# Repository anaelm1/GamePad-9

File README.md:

# GamePad 9

GamePad 9 is a 9 key macropad with a rotary encoder, an OLED Display. It uses KMK firmware

It is made as a dedicated macropad for gaming (first person or racing games etc).

## Features:
- 3D printed body with a honeycomb design to show the PCB. 
- 128x32 OLED Display.
- EC11 Rotary encoder to increase/decrease the volume, and skip to the next song.
- 9 Keys (Tab, W, E, A, S, D, Shift, Space, Control).

## CAD Model:
The pcb is attached to the base at a height of 2mm using 4 M3 screws for optimal support. The top plate is attached to the body using M3 screws and heat inserts in the 4 corners. 

It has 2 separate printed pieces. The base where the PCB sits, and the top cover. The project name and my name is engraved on the top plate as well.

Made in Fusion360. 

## PCB
Here's my PCB! It was made in KiCad.

Schematic

PCB

## Firmware Overview
This hackpad uses KMK firmware for everything. 

- the rotary encoder changes volume. press to next song.
- The 9 keys are Tab, W, E, A, S, D, Shift, Space, Control.
- The OLED is text. (Will change to an animation in the future)

## BOM:
These are the components used in the GamePad 9:

- 9x Cherry MX Switches.
- 9x DSA Keycaps.
- 4x M3x5x4 Heatset inserts.
- 8x M3x16mm Screws. (These might be changed if other screw sizes suit better)
- 9x 1N4148 DO-35 Diodes.
- 1x 0.91" 128x32 OLED Display
- 1x EC11 Rotary Encoder
- 1x XIAO RP2040
- 1x Case (2 printed parts)

## Info:
This macropad is made as part of the Hack Club Hackpad program!

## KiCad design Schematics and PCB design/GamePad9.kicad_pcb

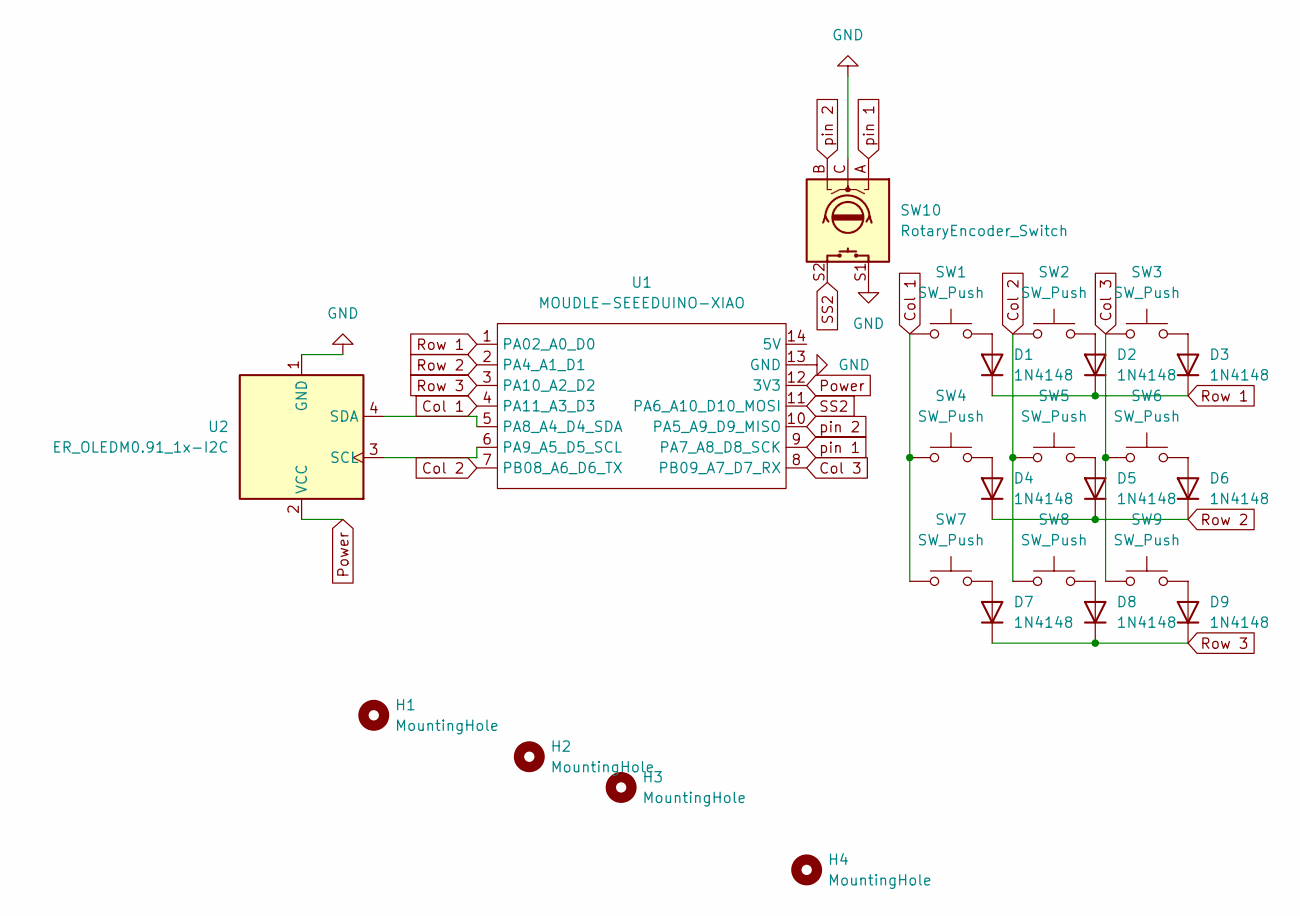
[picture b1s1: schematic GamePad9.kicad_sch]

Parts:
D1, D2, D3, D4, D5, D6, D7, D8, D9: 1N4148; D_DO-35_SOD27_P7.62mm_Horizontal
H1, H2, H3, H4: MountingHole; MountingHole_3.2mm_M3
SW1, SW2, SW3, SW4, SW5, SW6, SW7, SW8, SW9: SW_Push; SW_Cherry_MX_1.00u_PCB
SW10: RotaryEncoder_Switch; RotaryEncoder_Alps_EC11E-Switch_Vertical_H20mm
U1: MOUDLE-SEEEDUINO-XIAO; XIAO-Generic-Hybrid-14P-2.54-21X17.8MM
U2: ER_OLEDM0.91_1x-I2C

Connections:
Col 1: SW1.1, SW4.1, SW7.1, U1.4 (PA11_A3_D3)
Col 2: SW2.1, SW5.1, SW8.1, U1.7 (PB08_A6_D6_TX)
Col 3: SW3.1, SW6.1, SW9.1, U1.8 (PB09_A7_D7_RX)
GND: SW10.C, SW10.S1, U1.13 (GND), U2.1 (GND)
unnamed: D1.2 (A), SW1.2
unnamed: D2.2 (A), SW2.2
unnamed: D3.2 (A), SW3.2
unnamed: D4.2 (A), SW4.2
unnamed: D5.2 (A), SW5.2
unnamed: D6.2 (A), SW6.2
unnamed: D7.2 (A), SW7.2
unnamed: D8.2 (A), SW8.2
unnamed: D9.2 (A), SW9.2
unnamed: U1.5 (PA8_A4_D4_SDA), U2.4 (SDA)
unnamed: U1.6 (PA9_A5_D5_SCL), U2.3 (SCL)
Power: U1.12 (3V3), U2.2 (VCC)
Row 1: D1.1 (K), D2.1 (K), D3.1 (K), U1.1 (PA02_A0_D0)
Row 2: D4.1 (K), D5.1 (K), D6.1 (K), U1.2 (PA4_A1_D1)
Row 3: D7.1 (K), D8.1 (K), D9.1 (K), U1.3 (PA10_A2_D2)
SS2: SW10.S2, U1.11 (PA6_A10_D10_MOSI)
pin 1: SW10.A, U1.9 (PA7_A8_D8_SCK)
pin 2: SW10.B, U1.10 (PA5_A9_D9_MISO)

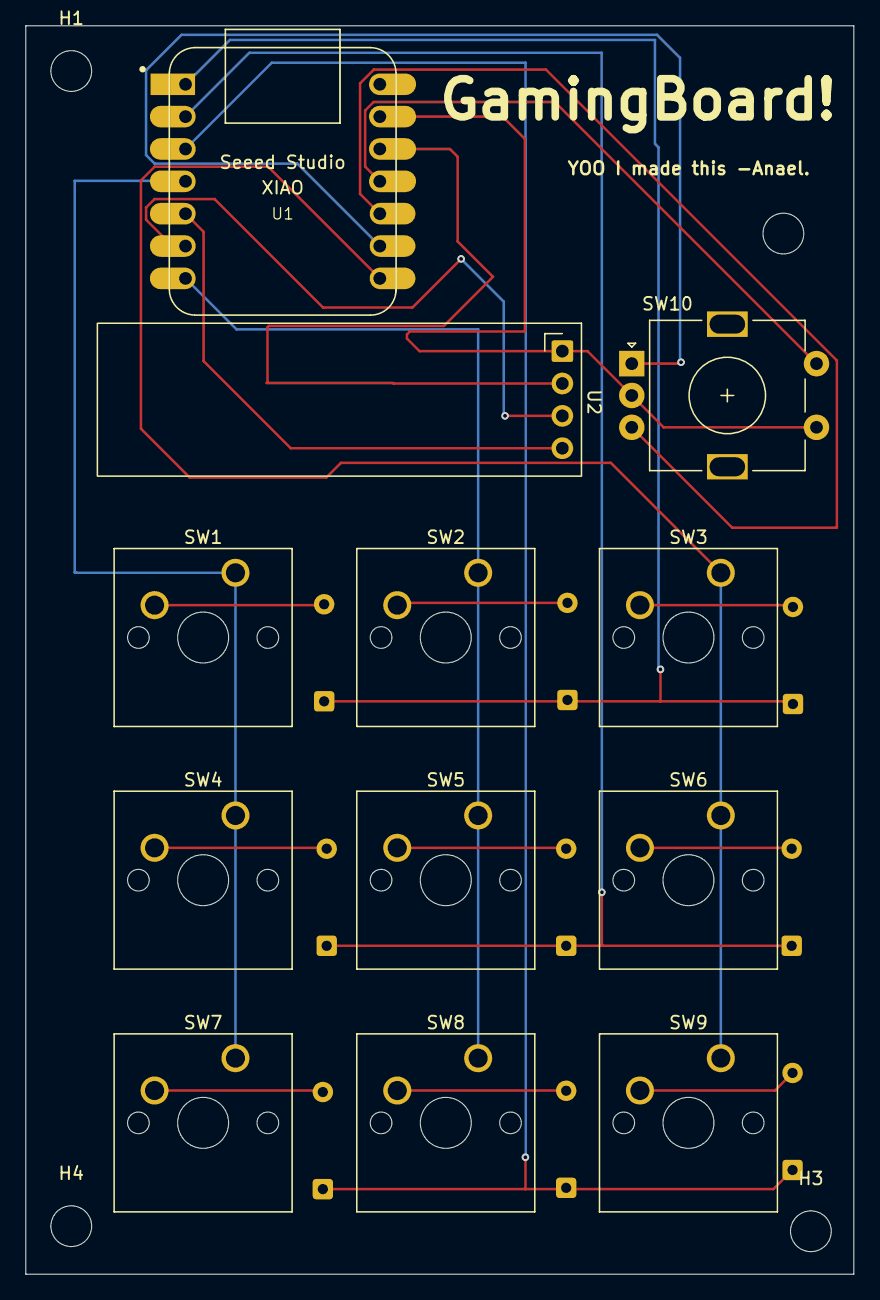
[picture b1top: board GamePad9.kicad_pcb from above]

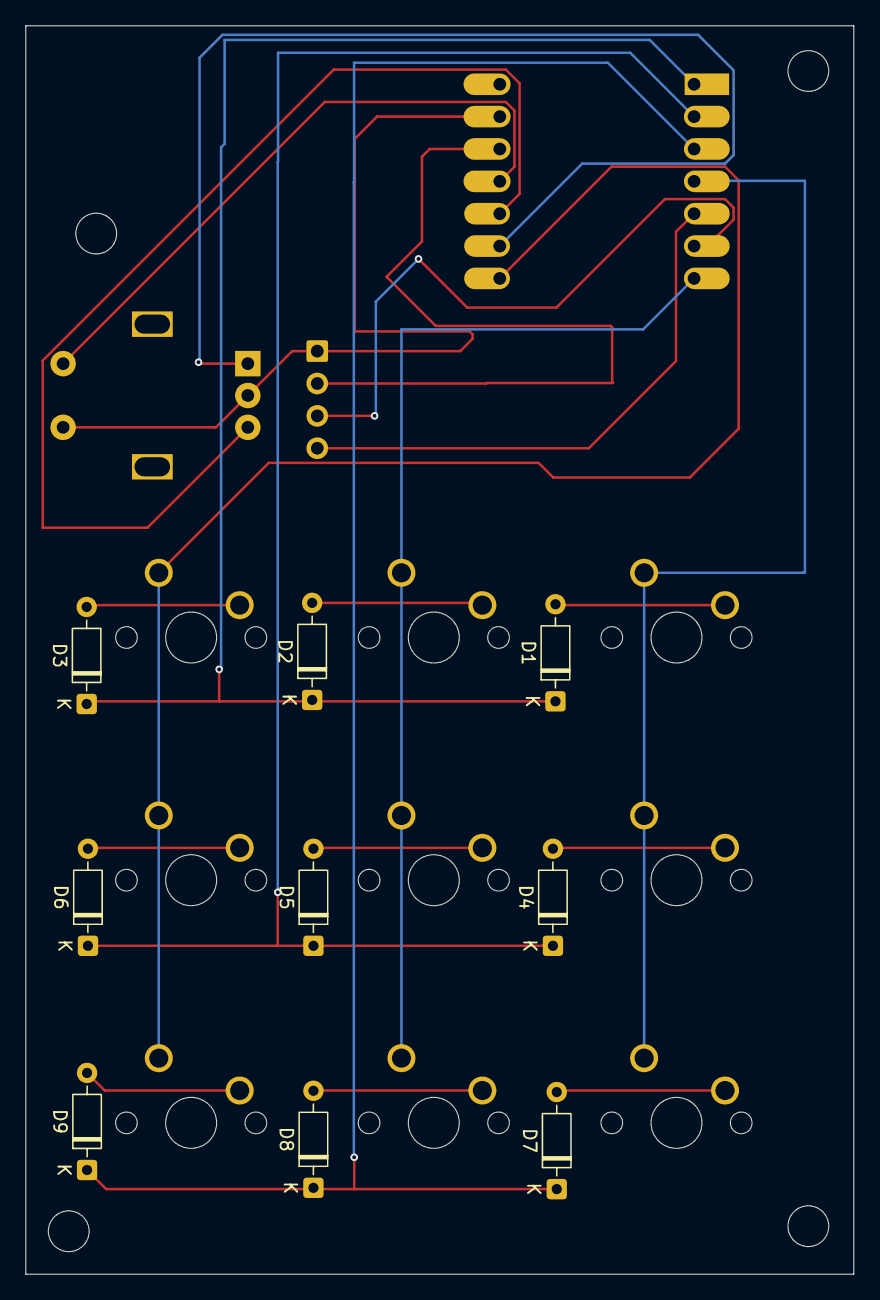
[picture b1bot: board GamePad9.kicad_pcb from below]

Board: 2 copper layers, 65.0 x 98.0 mm, 25 parts (9 on the bottom side), 22 nets.
